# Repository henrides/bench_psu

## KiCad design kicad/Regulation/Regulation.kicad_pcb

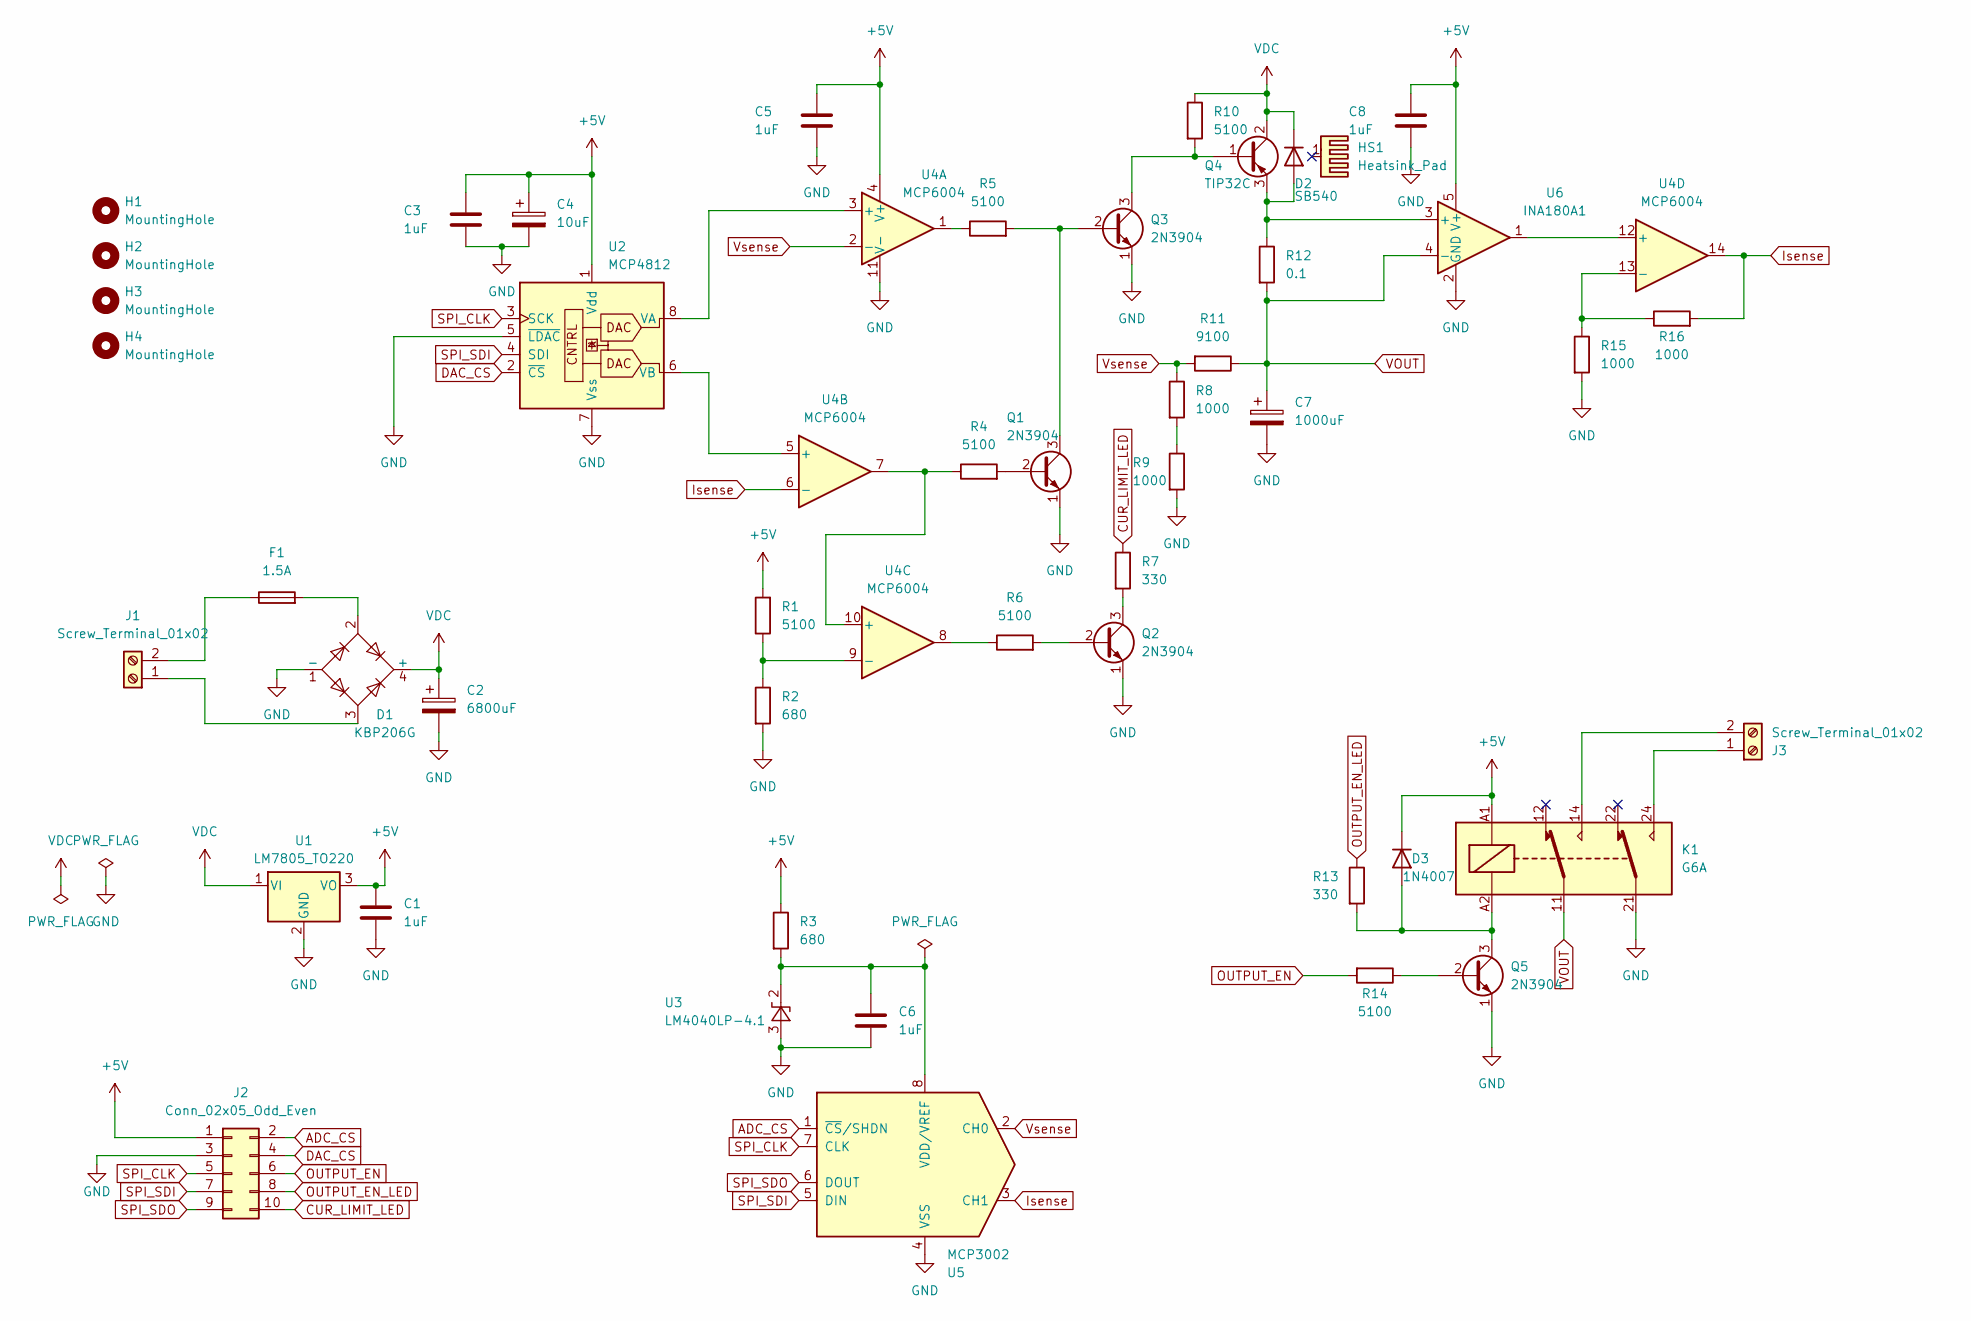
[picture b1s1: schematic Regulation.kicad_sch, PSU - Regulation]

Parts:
C1, C3, C5, C6, C8: 1uF; C_0805_2012Metric
C2: 6800uF; CP_Radial_D18.0mm_P7.50mm
C4: 10uF; CP_EIA-3216-18_Kemet-A_Pad1.58x1.35mm_HandSolder
C7: 1000uF; CP_Radial_D12.5mm_P5.00mm
D1: KBP206G; Diode_THT_Diode_Bridge_SIP365W86P406L1475H1060Q4
D2: SB540; D_DO-201AD_P12.70mm_Horizontal
D3: 1N4007; D_DO-41_SOD81_P7.62mm_Horizontal
F1: 1.5A; Fuseholder_Clip-6.3x32mm_Littelfuse_102_122_Inline_P34.21x7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
H1, H2, H3, H4: MountingHole; MountingHole_3.2mm_M3
HS1: Heatsink_Pad; Heatsink_Fischer_SK129-STS_42x25mm_2xDrill2.5mm
J1, J3: Screw_Terminal_01x02; TerminalBlock_RND_205-00012_1x02_P5.00mm_Horizontal
J2: Conn_02x05_Odd_Even; PinSocket_2x05_P2.54mm_Vertical
K1: G6A; Relay_DPDT_Omron_G6A
Q1, Q2, Q3, Q5: 2N3904; TO-92_Inline_Wide
Q4: TIP32C; TO-220-3_Vertical
R1, R4, R5, R6, R10, R14: 5100; R_0805_2012Metric
R2, R3: 680; R_0805_2012Metric
R7, R13: 330; R_0805_2012Metric
R8, R9, R15, R16: 1000; R_0805_2012Metric
R11: 9100; R_0805_2012Metric
R12: 0.1; R_Bare_Metal_Element_L16.3mm_W4.0mm_no_mask
U1: LM7805_TO220; TO-220-3_Vertical
U2: MCP4812; DIP-8_W7.62mm
U3: LM4040LP-4.1; TO-92_Inline
U4: MCP6004; DIP-14_W7.62mm
U5: MCP3002; DIP-8_W7.62mm
U6: INA180A1; SOT-23-5_HandSoldering

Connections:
+5V: C1.1, C3.1, C4.1, C5.1, C8.1, D3.1 (K), J2.1, K1.A1, R1.2, R3.1, U1.3 (VO), U2.1 (Vdd), U4.4 (V+), U6.5 (V+)
ADC_CS: J2.2, U5.1 (~CS/SHDN)
CUR_LIMIT_LED: J2.10, R7.1
DAC_CS: J2.4, U2.2 (~CS)
GND: C1.2, C2.2, C3.2, C4.2, C5.2, C6.2, C7.2, C8.2, D1.1 (-), J2.3, K1.21, Q1.1 (E), Q2.1 (E), Q3.1 (E), Q5.1 (E), R2.2, R9.2, R15.2, U1.2 (GND), U2.5 (~LDAC), U2.7 (Vss), U3.3 (A), U4.11 (V-), U5.4 (VSS), U6.2 (GND)
Isense: R16.2, U4.6 (-), U4.14, U5.3 (CH1)
unnamed: D1.2, F1.2
unnamed: D2.2 (A), Q4.3 (E), R12.1, U6.3 (+)
unnamed: D3.2 (A), K1.A2, Q5.3 (C), R13.2
unnamed: D1.3, J1.1
unnamed: F1.1, J1.2
unnamed: J3.1, K1.24
unnamed: J3.2, K1.14
unnamed: Q1.2 (B), R4.2
unnamed: Q1.3 (C), Q3.2 (B), R5.2
unnamed: Q2.2 (B), R6.2
unnamed: Q2.3 (C), R7.2
unnamed: Q3.3 (C), Q4.1 (B), R10.2
unnamed: Q5.2 (B), R14.1
unnamed: R5.1, U4.1
unnamed: R6.1, U4.8
unnamed: R8.2, R9.1
unnamed: U2.8 (VA), U4.3 (+)
unnamed: U2.6 (VB), U4.5 (+)
unnamed: C6.1, R3.2, U3.2 (K), U5.8 (VDD/VREF)
unnamed: R4.1, U4.7, U4.10 (+)
unnamed: R1.1, R2.1, U4.9 (-)
unnamed: U4.12 (+), U6.1
unnamed: R15.1, R16.1, U4.13 (-)
OUTPUT_EN: J2.6, R14.2
OUTPUT_EN_LED: J2.8, R13.1
SPI_CLK: J2.5, U2.3 (SCK), U5.7 (CLK)
SPI_SDI: J2.7, U2.4 (SDI), U5.5 (DIN)
SPI_SDO: J2.9, U5.6 (DOUT)
VDC: C2.1, D1.4 (+), D2.1 (K), Q4.2 (C), R10.1, U1.1 (VI)
VOUT: C7.1, K1.11, R11.1, R12.2, U6.4 (-)
Vsense: R8.1, R11.2, U4.2 (-), U5.2 (CH0)

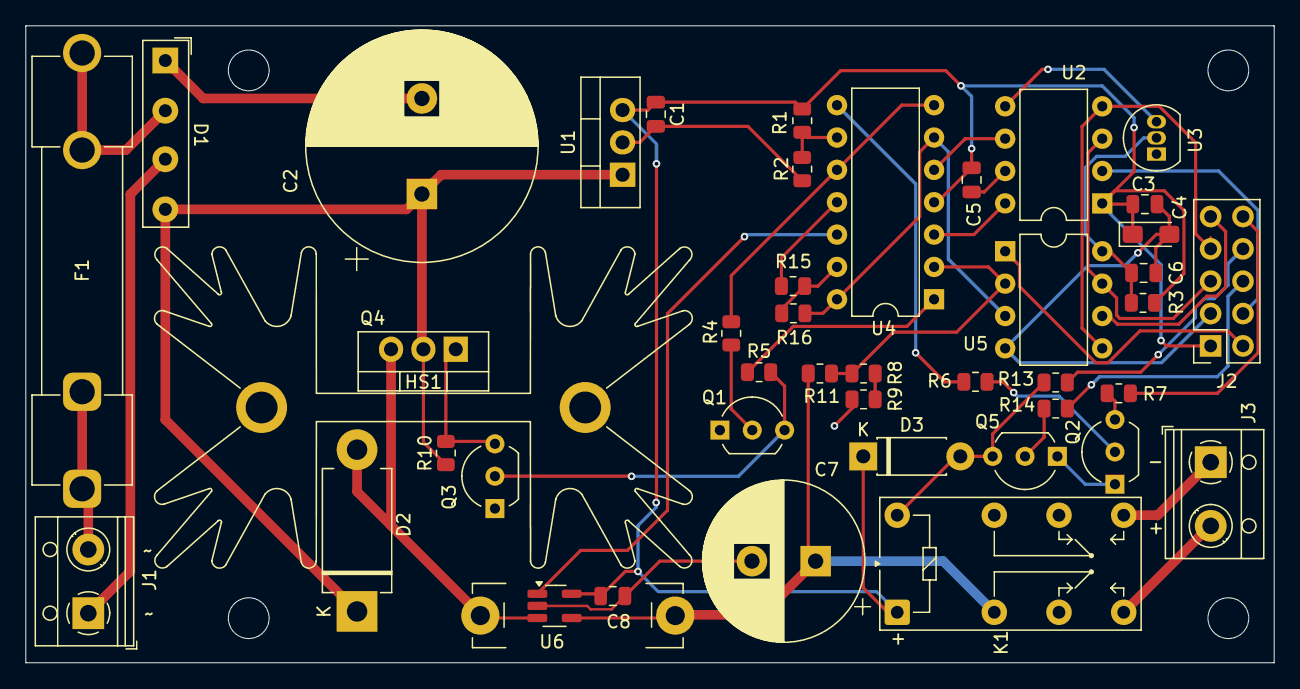
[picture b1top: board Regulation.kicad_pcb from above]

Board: 2 copper layers, 98.0 x 50.0 mm, 48 parts (0 on the bottom side), 37 nets.

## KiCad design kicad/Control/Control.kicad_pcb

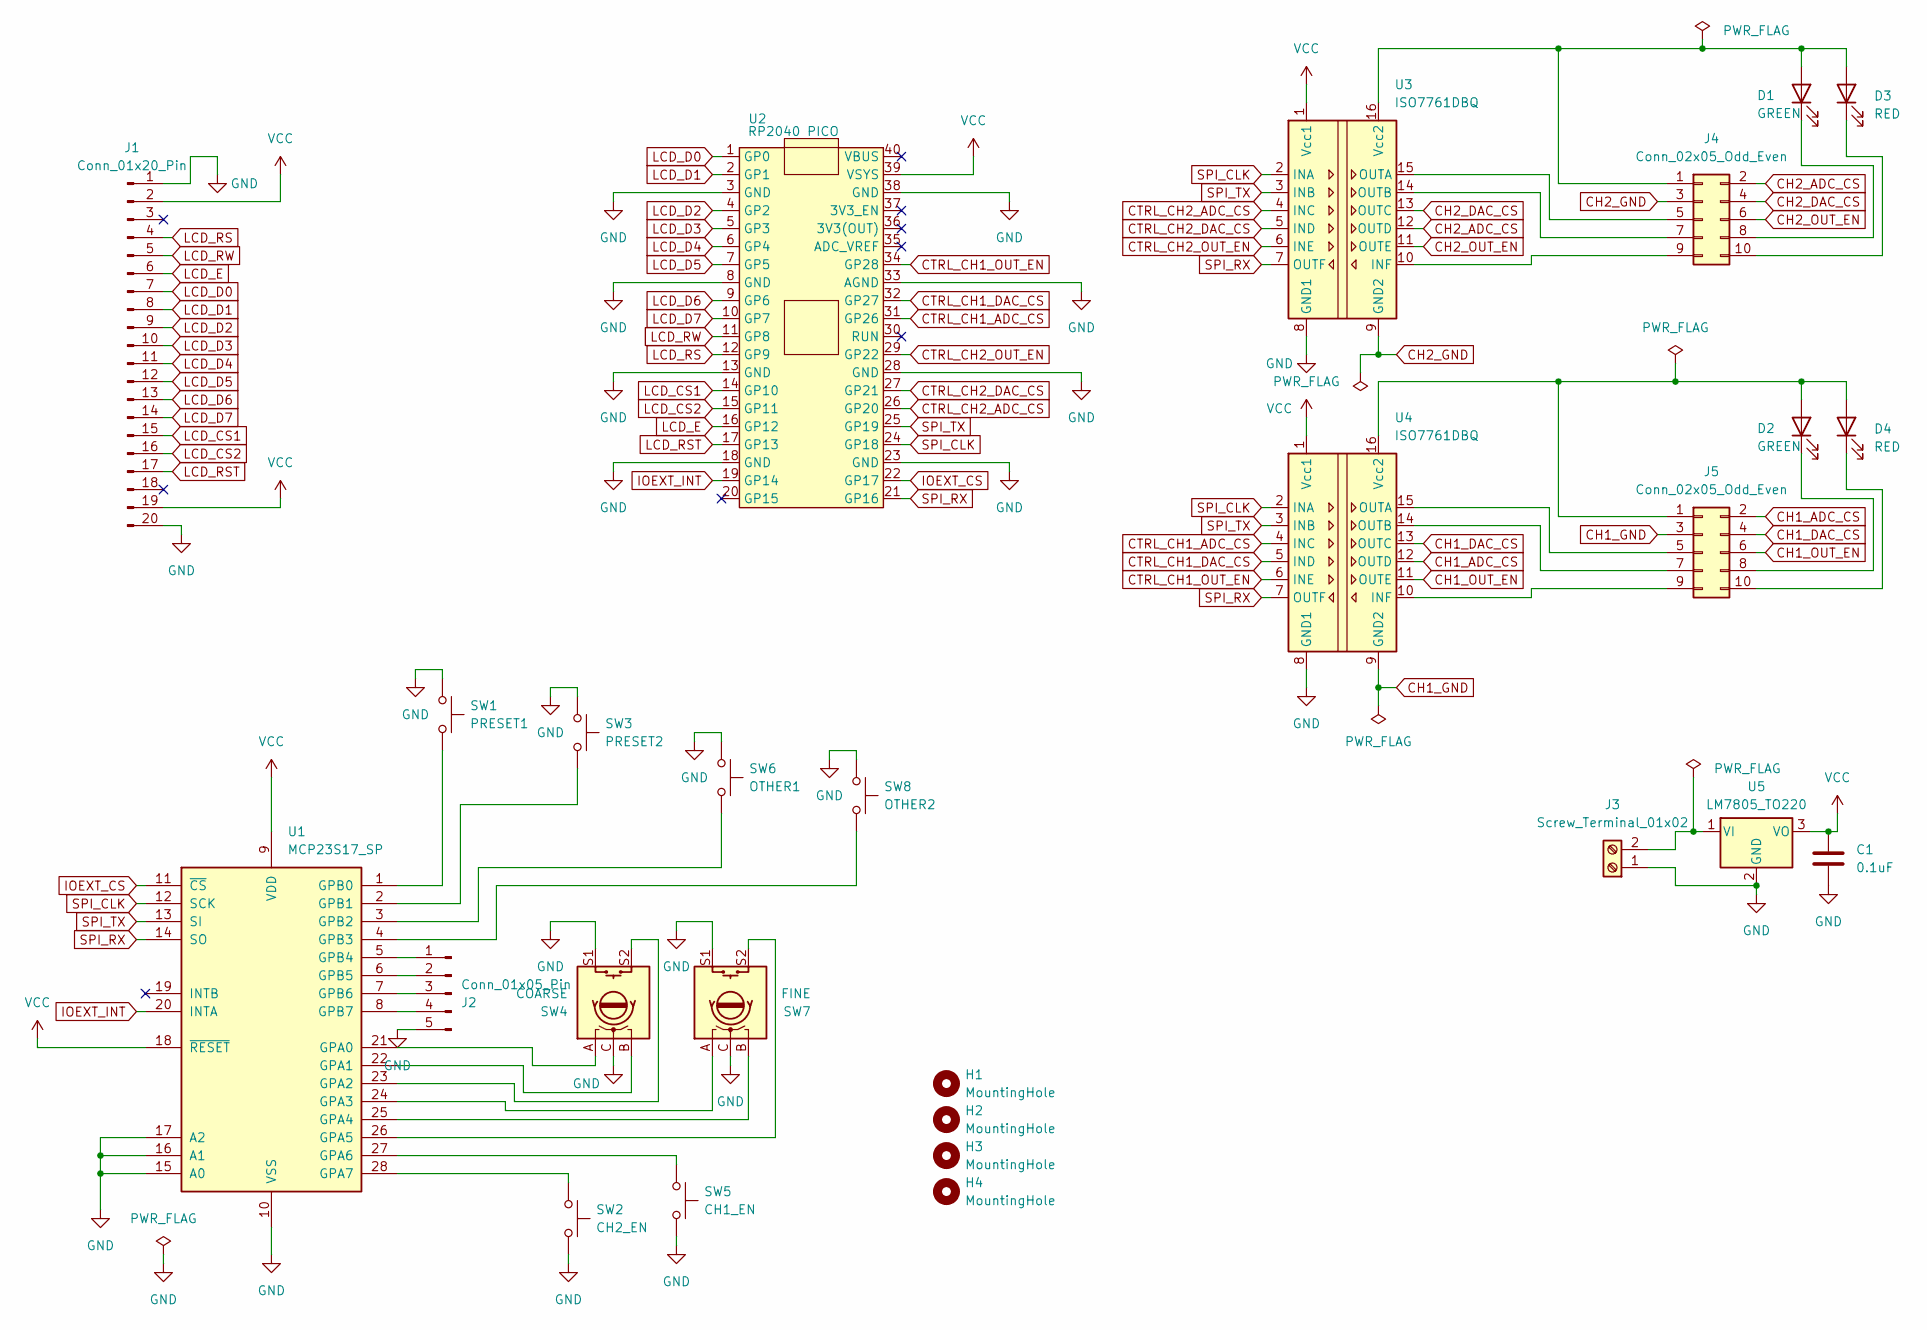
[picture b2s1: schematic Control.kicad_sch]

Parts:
C1: 0.1uF; C_0805_2012Metric
D1, D2: GREEN; LED_D5.0mm
D3, D4: RED; LED_D5.0mm
H1, H2, H3, H4: MountingHole; MountingHole_3.2mm_M3
J1: Conn_01x20_Pin; PinSocket_1x20_P2.54mm_Vertical
J2: Conn_01x05_Pin; PinHeader_1x05_P2.54mm_Vertical
J3: Screw_Terminal_01x02; TerminalBlock_RND_205-00012_1x02_P5.00mm_Horizontal
J4, J5: Conn_02x05_Odd_Even; Connector Header 2x05
SW1: PRESET1; SW_PUSH_6mm_H13mm
SW2: CH2_EN; SW_PUSH_6mm_H13mm
SW3: PRESET2; SW_PUSH_6mm_H13mm
SW4: COARSE; RotaryEncoder_Alps_EC11E-Switch_Vertical_H20mm_CircularMoun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
SW5: CH1_EN; SW_PUSH_6mm_H13mm
SW6: OTHER1; SW_PUSH_6mm_H13mm
SW7: FINE; RotaryEncoder_Alps_EC11E-Switch_Vertical_H20mm_CircularMoun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
SW8: OTHER2; SW_PUSH_6mm_H13mm
U1: MCP23S17_SP; DIP-28_W7.62mm
U2: RP2040 PICO; Raspberry_Pi_Pico_Headers
U3, U4: ISO7761DBQ; SSOP-16_3.9x4.9mm_P0.635mm
U5: LM7805_TO220; TO-220-3_Vertical

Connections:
CH1_ADC_CS: J5.2, U4.12 (OUTD)
CH1_DAC_CS: J5.4, U4.13 (OUTC)
CH1_GND: J5.3, U4.9 (GND2)
CH1_OUT_EN: J5.6, U4.11 (OUTE)
CH2_ADC_CS: J4.2, U3.12 (OUTD)
CH2_DAC_CS: J4.4, U3.13 (OUTC)
CH2_GND: J4.3, U3.9 (GND2)
CH2_OUT_EN: J4.6, U3.11 (OUTE)
CTRL_CH1_ADC_CS: U2.31 (GP26), U4.4 (INC)
CTRL_CH1_DAC_CS: U2.32 (GP27), U4.5 (IND)
CTRL_CH1_OUT_EN: U2.34 (GP28), U4.6 (INE)
CTRL_CH2_ADC_CS: U2.26 (GP20), U3.4 (INC)
CTRL_CH2_DAC_CS: U2.27 (GP21), U3.5 (IND)
CTRL_CH2_OUT_EN: U2.29 (GP22), U3.6 (INE)
GND: C1.2, J1.1, J1.20, J2.5, J3.1, SW1.1, SW2.2, SW3.1, SW4.C, SW4.S1, SW5.2, SW6.1, SW7.C, SW7.S1, SW8.1, U1.10 (VSS), U1.15 (A0), U1.16 (A1), U1.17 (A2), U2.3 (GND), U2.8 (GND), U2.13 (GND), U2.18 (GND), U2.23 (GND), U2.28 (GND), U2.33 (AGND), U2.38 (GND), U3.8 (GND1), U4.8 (GND1), U5.2 (GND)
IOEXT_CS: U1.11 (~CS), U2.22 (GP17)
IOEXT_INT: U1.20 (INTA), U2.19 (GP14)
LCD_CS1: J1.15, U2.14 (GP10)
LCD_CS2: J1.16, U2.15 (GP11)
LCD_D0: J1.7, U2.1 (GP0)
LCD_D1: J1.8, U2.2 (GP1)
LCD_D2: J1.9, U2.4 (GP2)
LCD_D3: J1.10, U2.5 (GP3)
LCD_D4: J1.11, U2.6 (GP4)
LCD_D5: J1.12, U2.7 (GP5)
LCD_D6: J1.13, U2.9 (GP6)
LCD_D7: J1.14, U2.10 (GP7)
LCD_E: J1.6, U2.16 (GP12)
LCD_RS: J1.4, U2.12 (GP9)
LCD_RST: J1.17, U2.17 (GP13)
LCD_RW: J1.5, U2.11 (GP8)
unnamed: D1.2 (A), D3.2 (A), J4.1, U3.16 (Vcc2)
unnamed: D1.1 (K), J4.8
unnamed: D2.2 (A), D4.2 (A), J5.1, U4.16 (Vcc2)
unnamed: D2.1 (K), J5.8
unnamed: D3.1 (K), J4.10
unnamed: D4.1 (K), J5.10
unnamed: J2.1, U1.5 (GPB4)
unnamed: J2.2, U1.6 (GPB5)
unnamed: J2.3, U1.7 (GPB6)
unnamed: J2.4, U1.8 (GPB7)
unnamed: J3.2, U5.1 (VI)
unnamed: J4.5, U3.15 (OUTA)
unnamed: J4.7, U3.14 (OUTB)
unnamed: J4.9, U3.10 (INF)
unnamed: J5.5, U4.15 (OUTA)
unnamed: J5.7, U4.14 (OUTB)
unnamed: J5.9, U4.10 (INF)
unnamed: SW4.A, U1.21 (GPA0)
unnamed: SW4.B, U1.22 (GPA1)
unnamed: SW4.S2, U1.23 (GPA2)
unnamed: SW7.A, U1.24 (GPA3)
unnamed: SW7.B, U1.25 (GPA4)
unnamed: SW7.S2, U1.26 (GPA5)
unnamed: SW5.1, U1.27 (GPA6)
unnamed: SW2.1, U1.28 (GPA7)
unnamed: SW1.2, U1.1 (GPB0)
unnamed: SW3.2, U1.2 (GPB1)
unnamed: SW6.2, U1.3 (GPB2)
unnamed: SW8.2, U1.4 (GPB3)
SPI_CLK: U1.12 (SCK), U2.24 (GP18), U3.2 (INA), U4.2 (INA)
SPI_RX: U1.14 (SO), U2.21 (GP16), U3.7 (OUTF), U4.7 (OUTF)
SPI_TX: U1.13 (SI), U2.25 (GP19), U3.3 (INB), U4.3 (INB)
VCC: C1.1, J1.2, J1.19, U1.9 (VDD), U1.18 (~RESET), U2.39 (VSYS), U3.1 (Vcc1), U4.1 (Vcc1), U5.3 (VO)

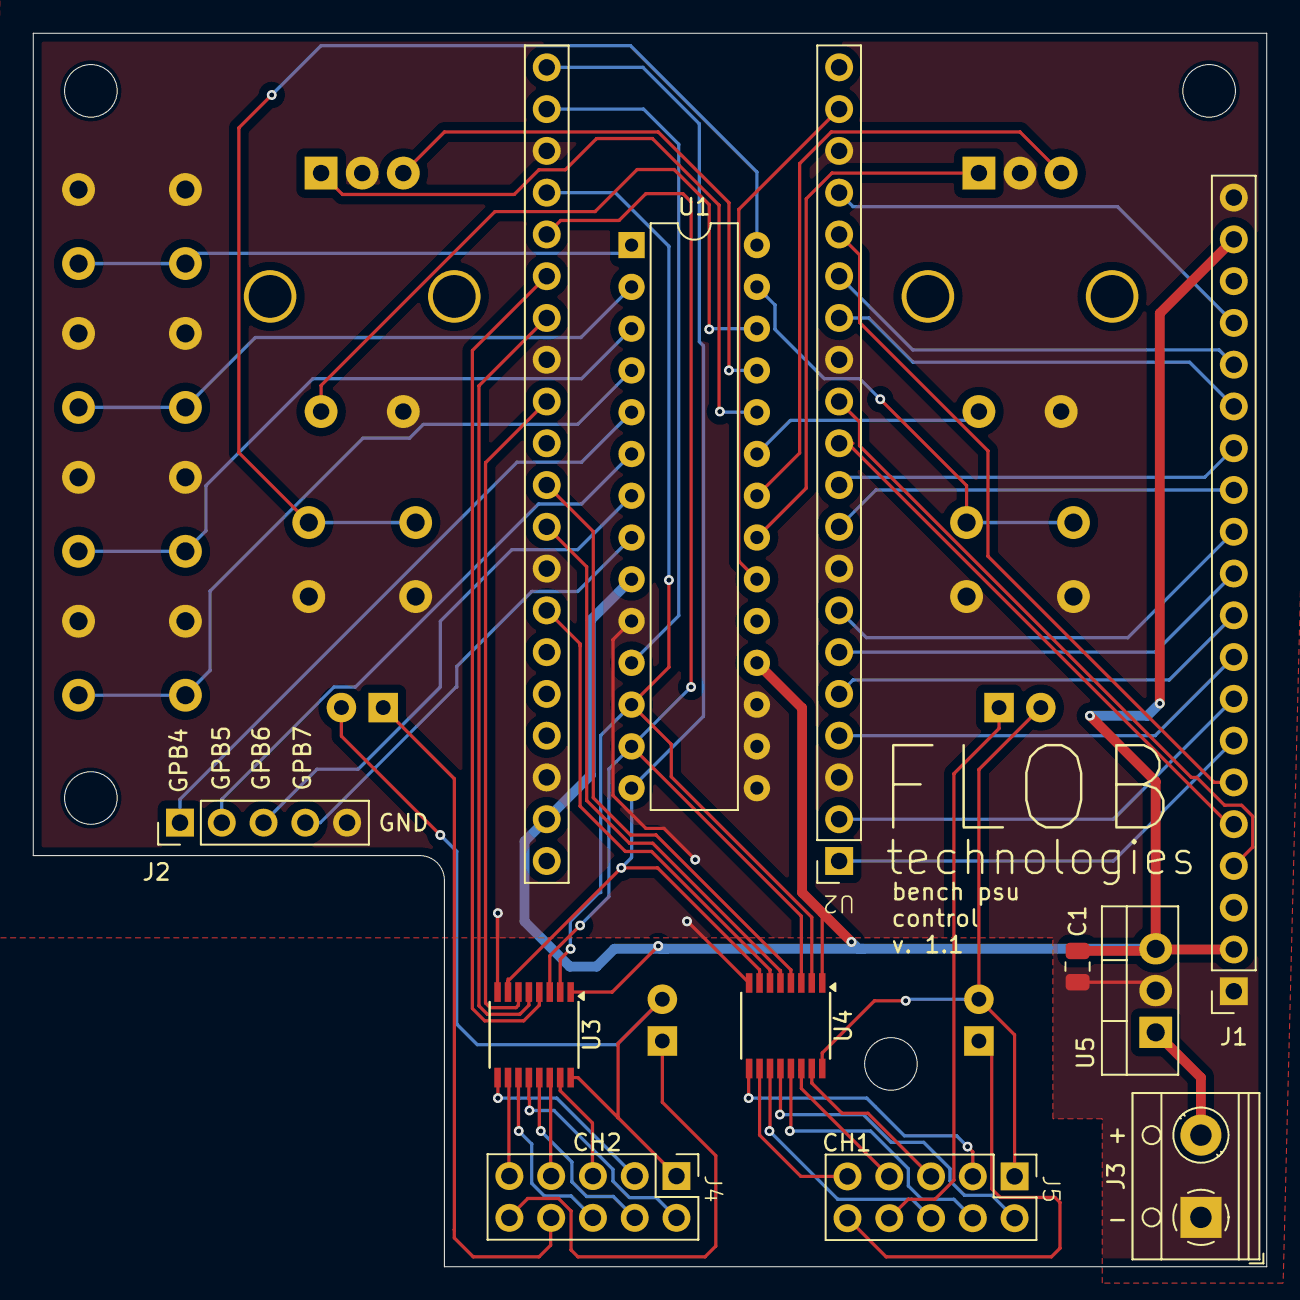
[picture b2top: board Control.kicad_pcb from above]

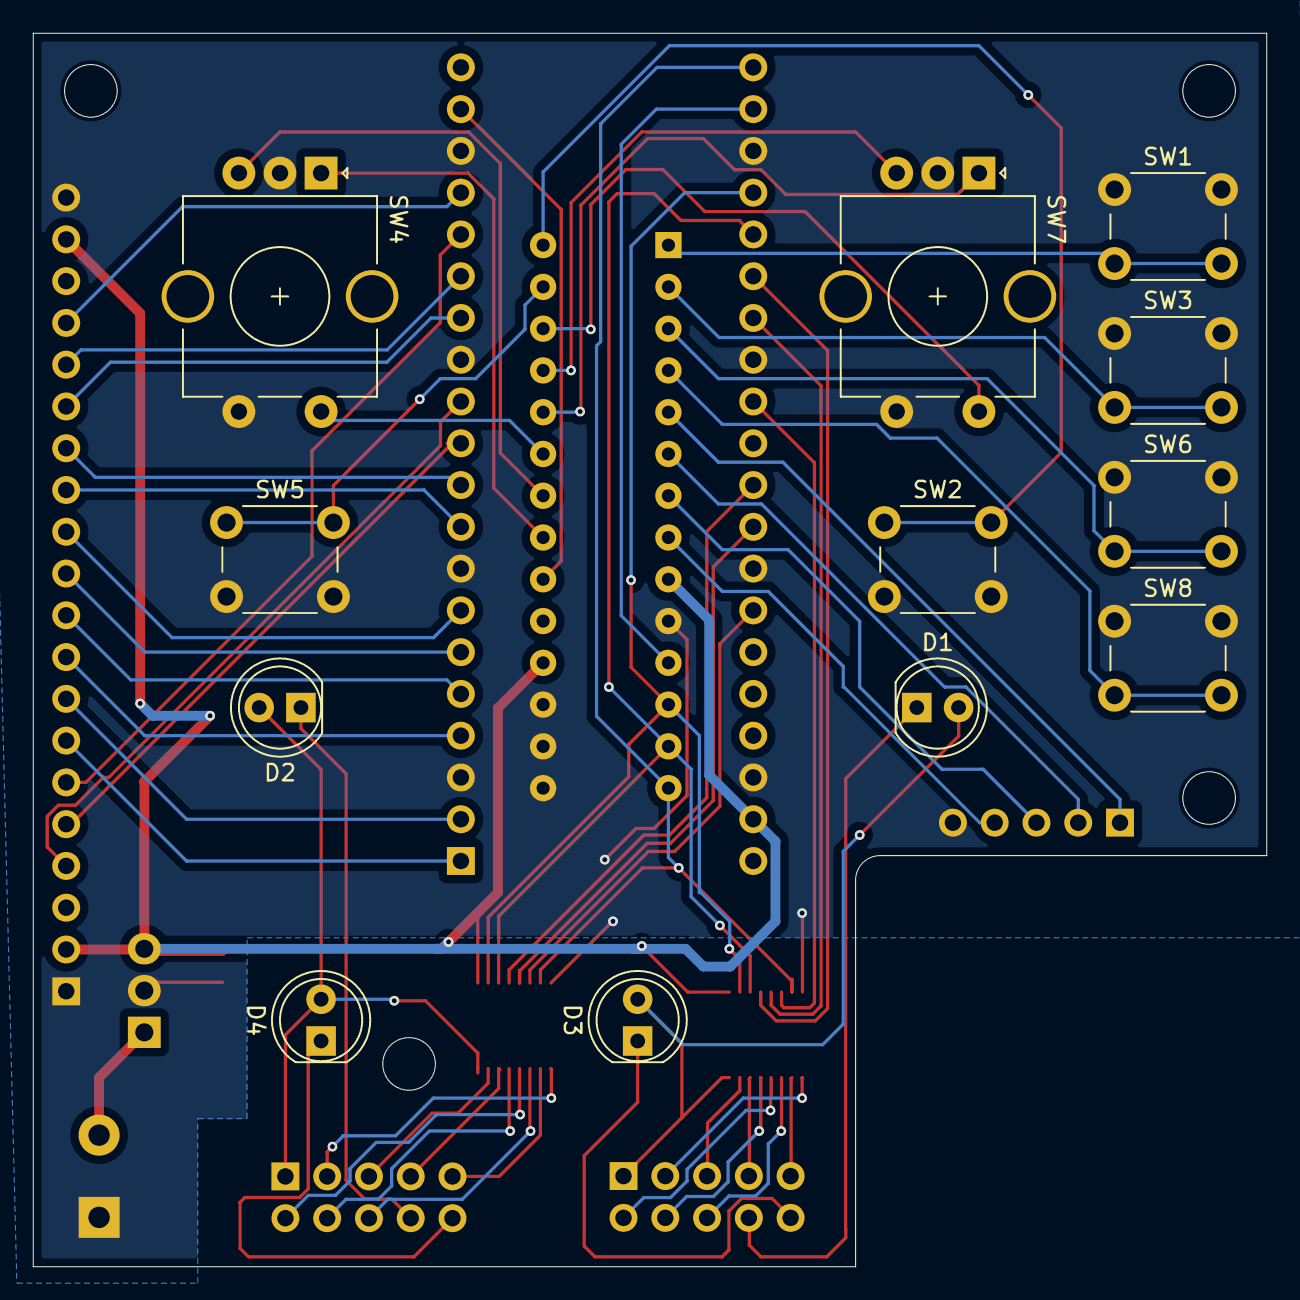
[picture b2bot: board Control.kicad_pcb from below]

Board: 2 copper layers, 75.0 x 75.0 mm, 27 parts (12 on the bottom side), 64 nets.

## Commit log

2025-02-28 Change channel header when enabling output
2025-02-28 Integrate kicad models
2025-03-02 Reference channels by name instead of index
2025-05-29 Add preset support
2025-05-29 Fix control connectors spacing
2025-05-29 Update .gitignore for project specific ignores
